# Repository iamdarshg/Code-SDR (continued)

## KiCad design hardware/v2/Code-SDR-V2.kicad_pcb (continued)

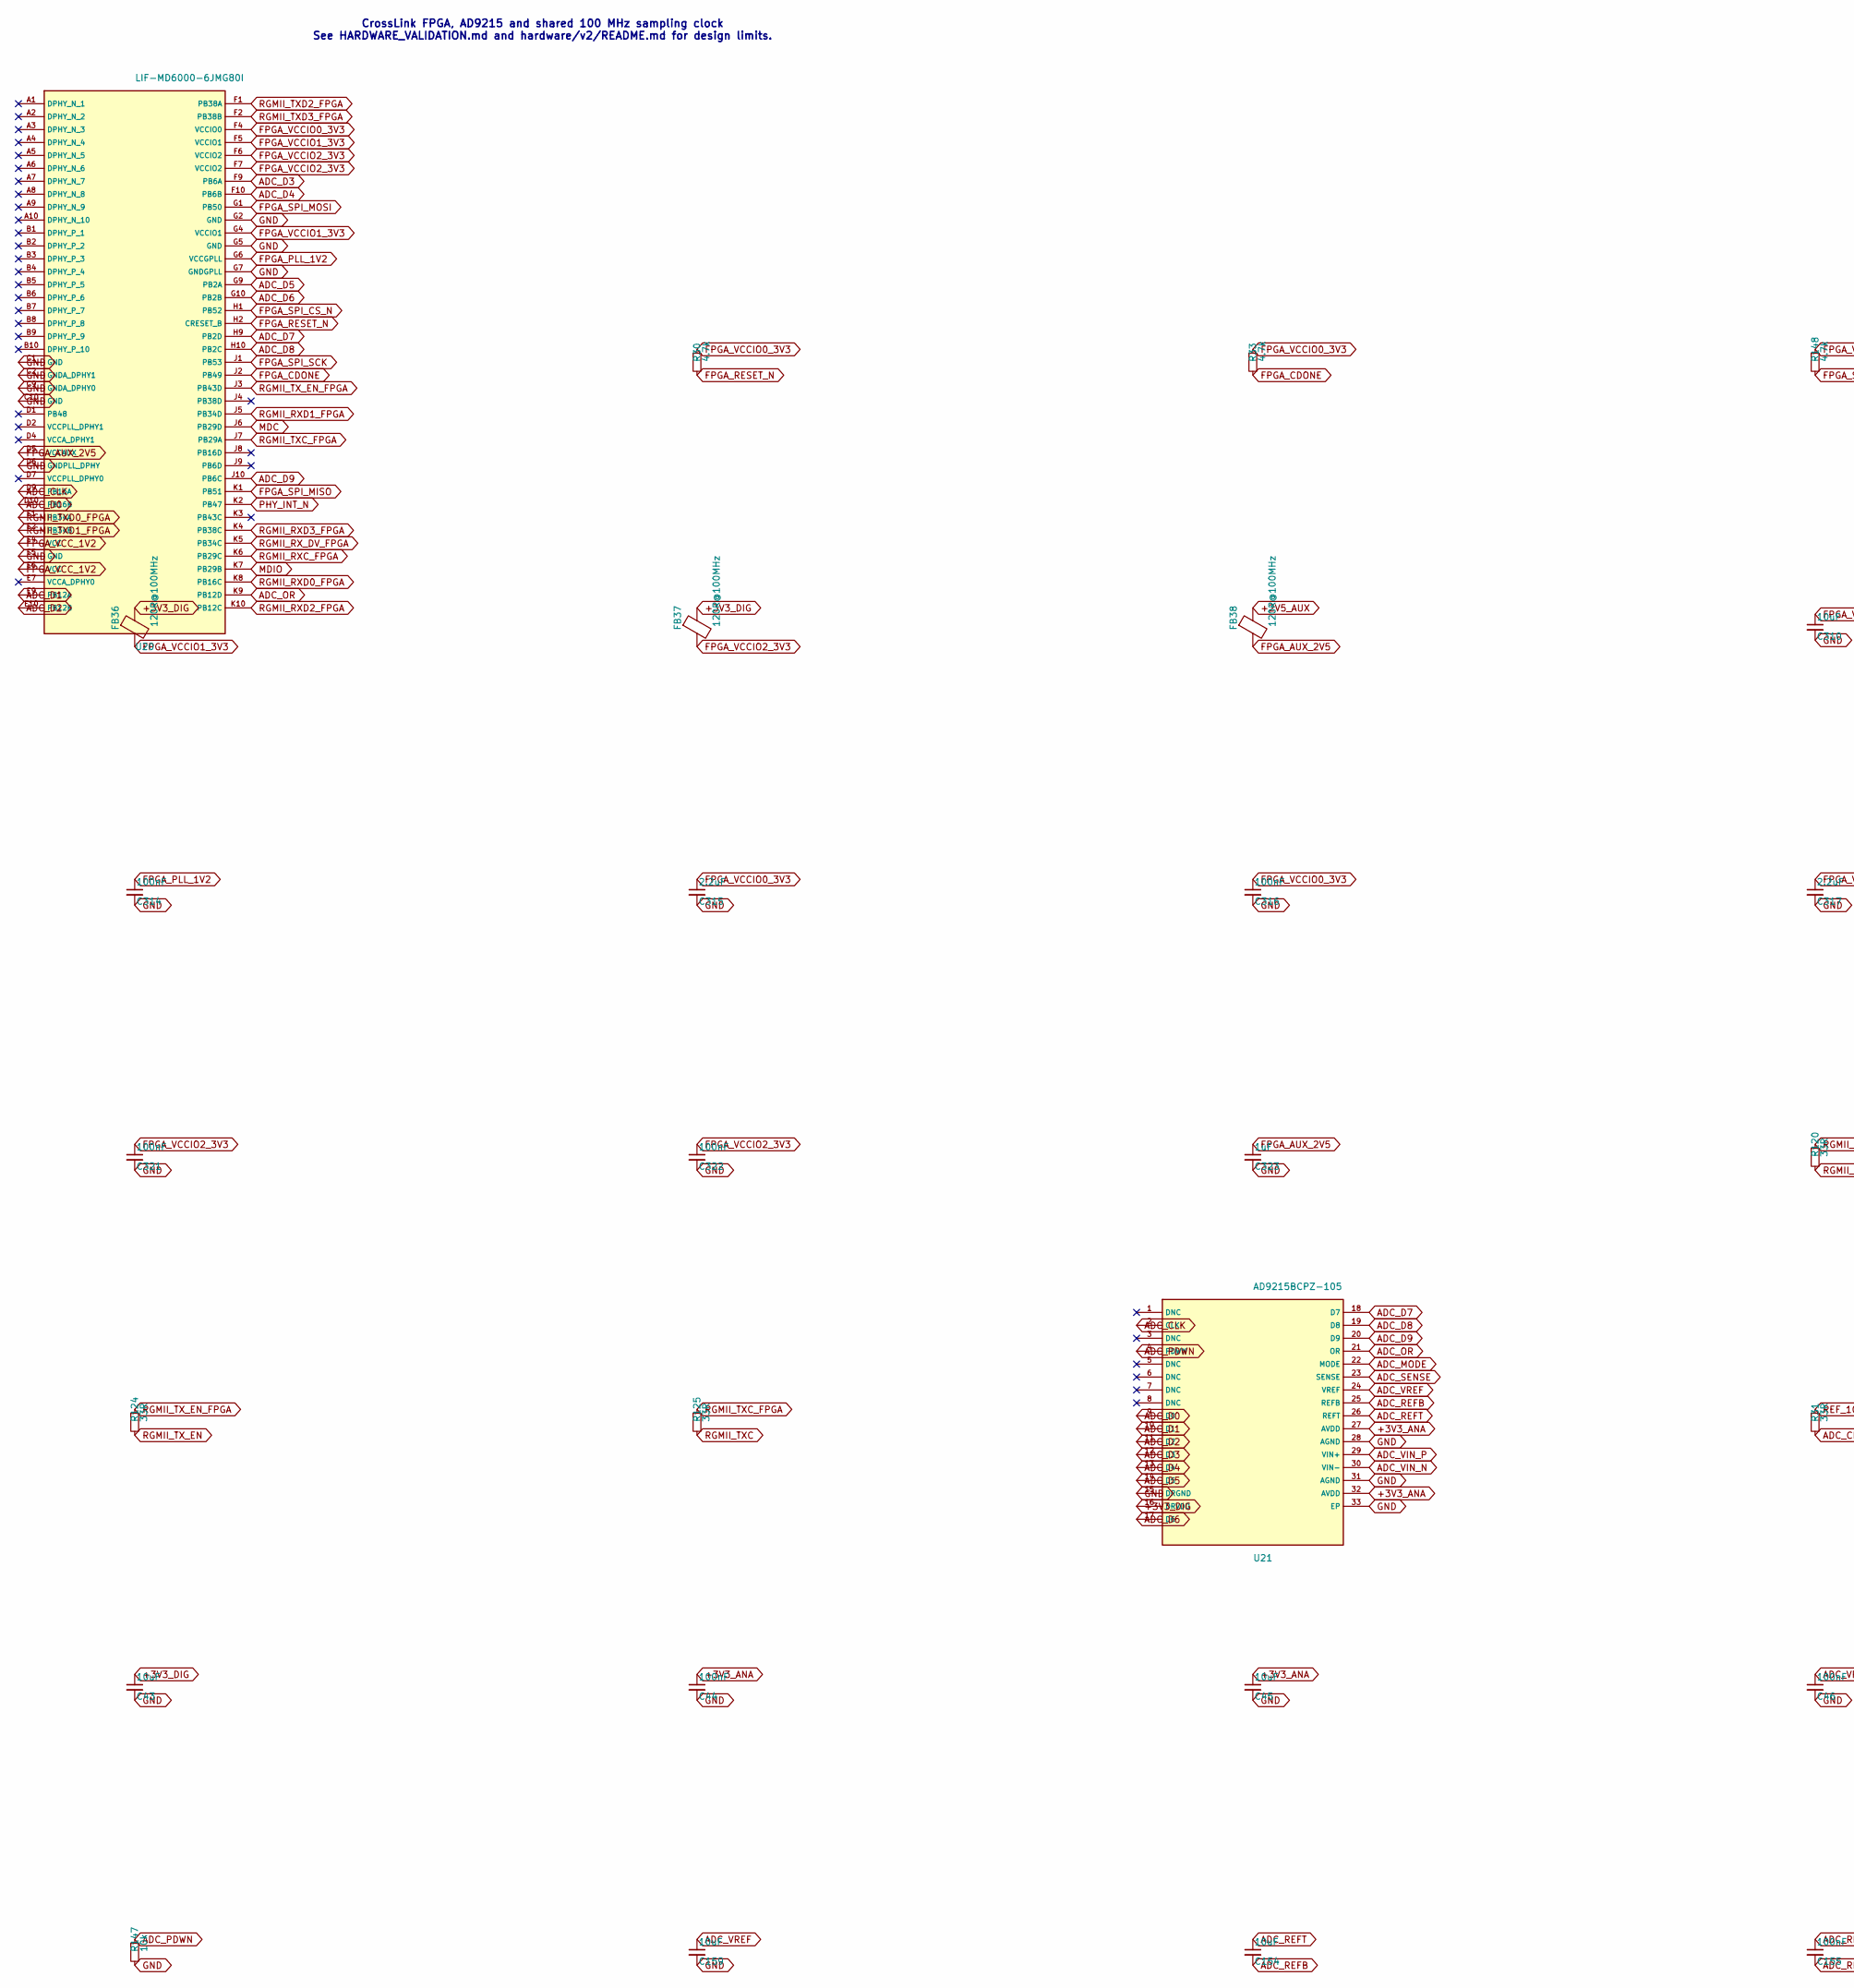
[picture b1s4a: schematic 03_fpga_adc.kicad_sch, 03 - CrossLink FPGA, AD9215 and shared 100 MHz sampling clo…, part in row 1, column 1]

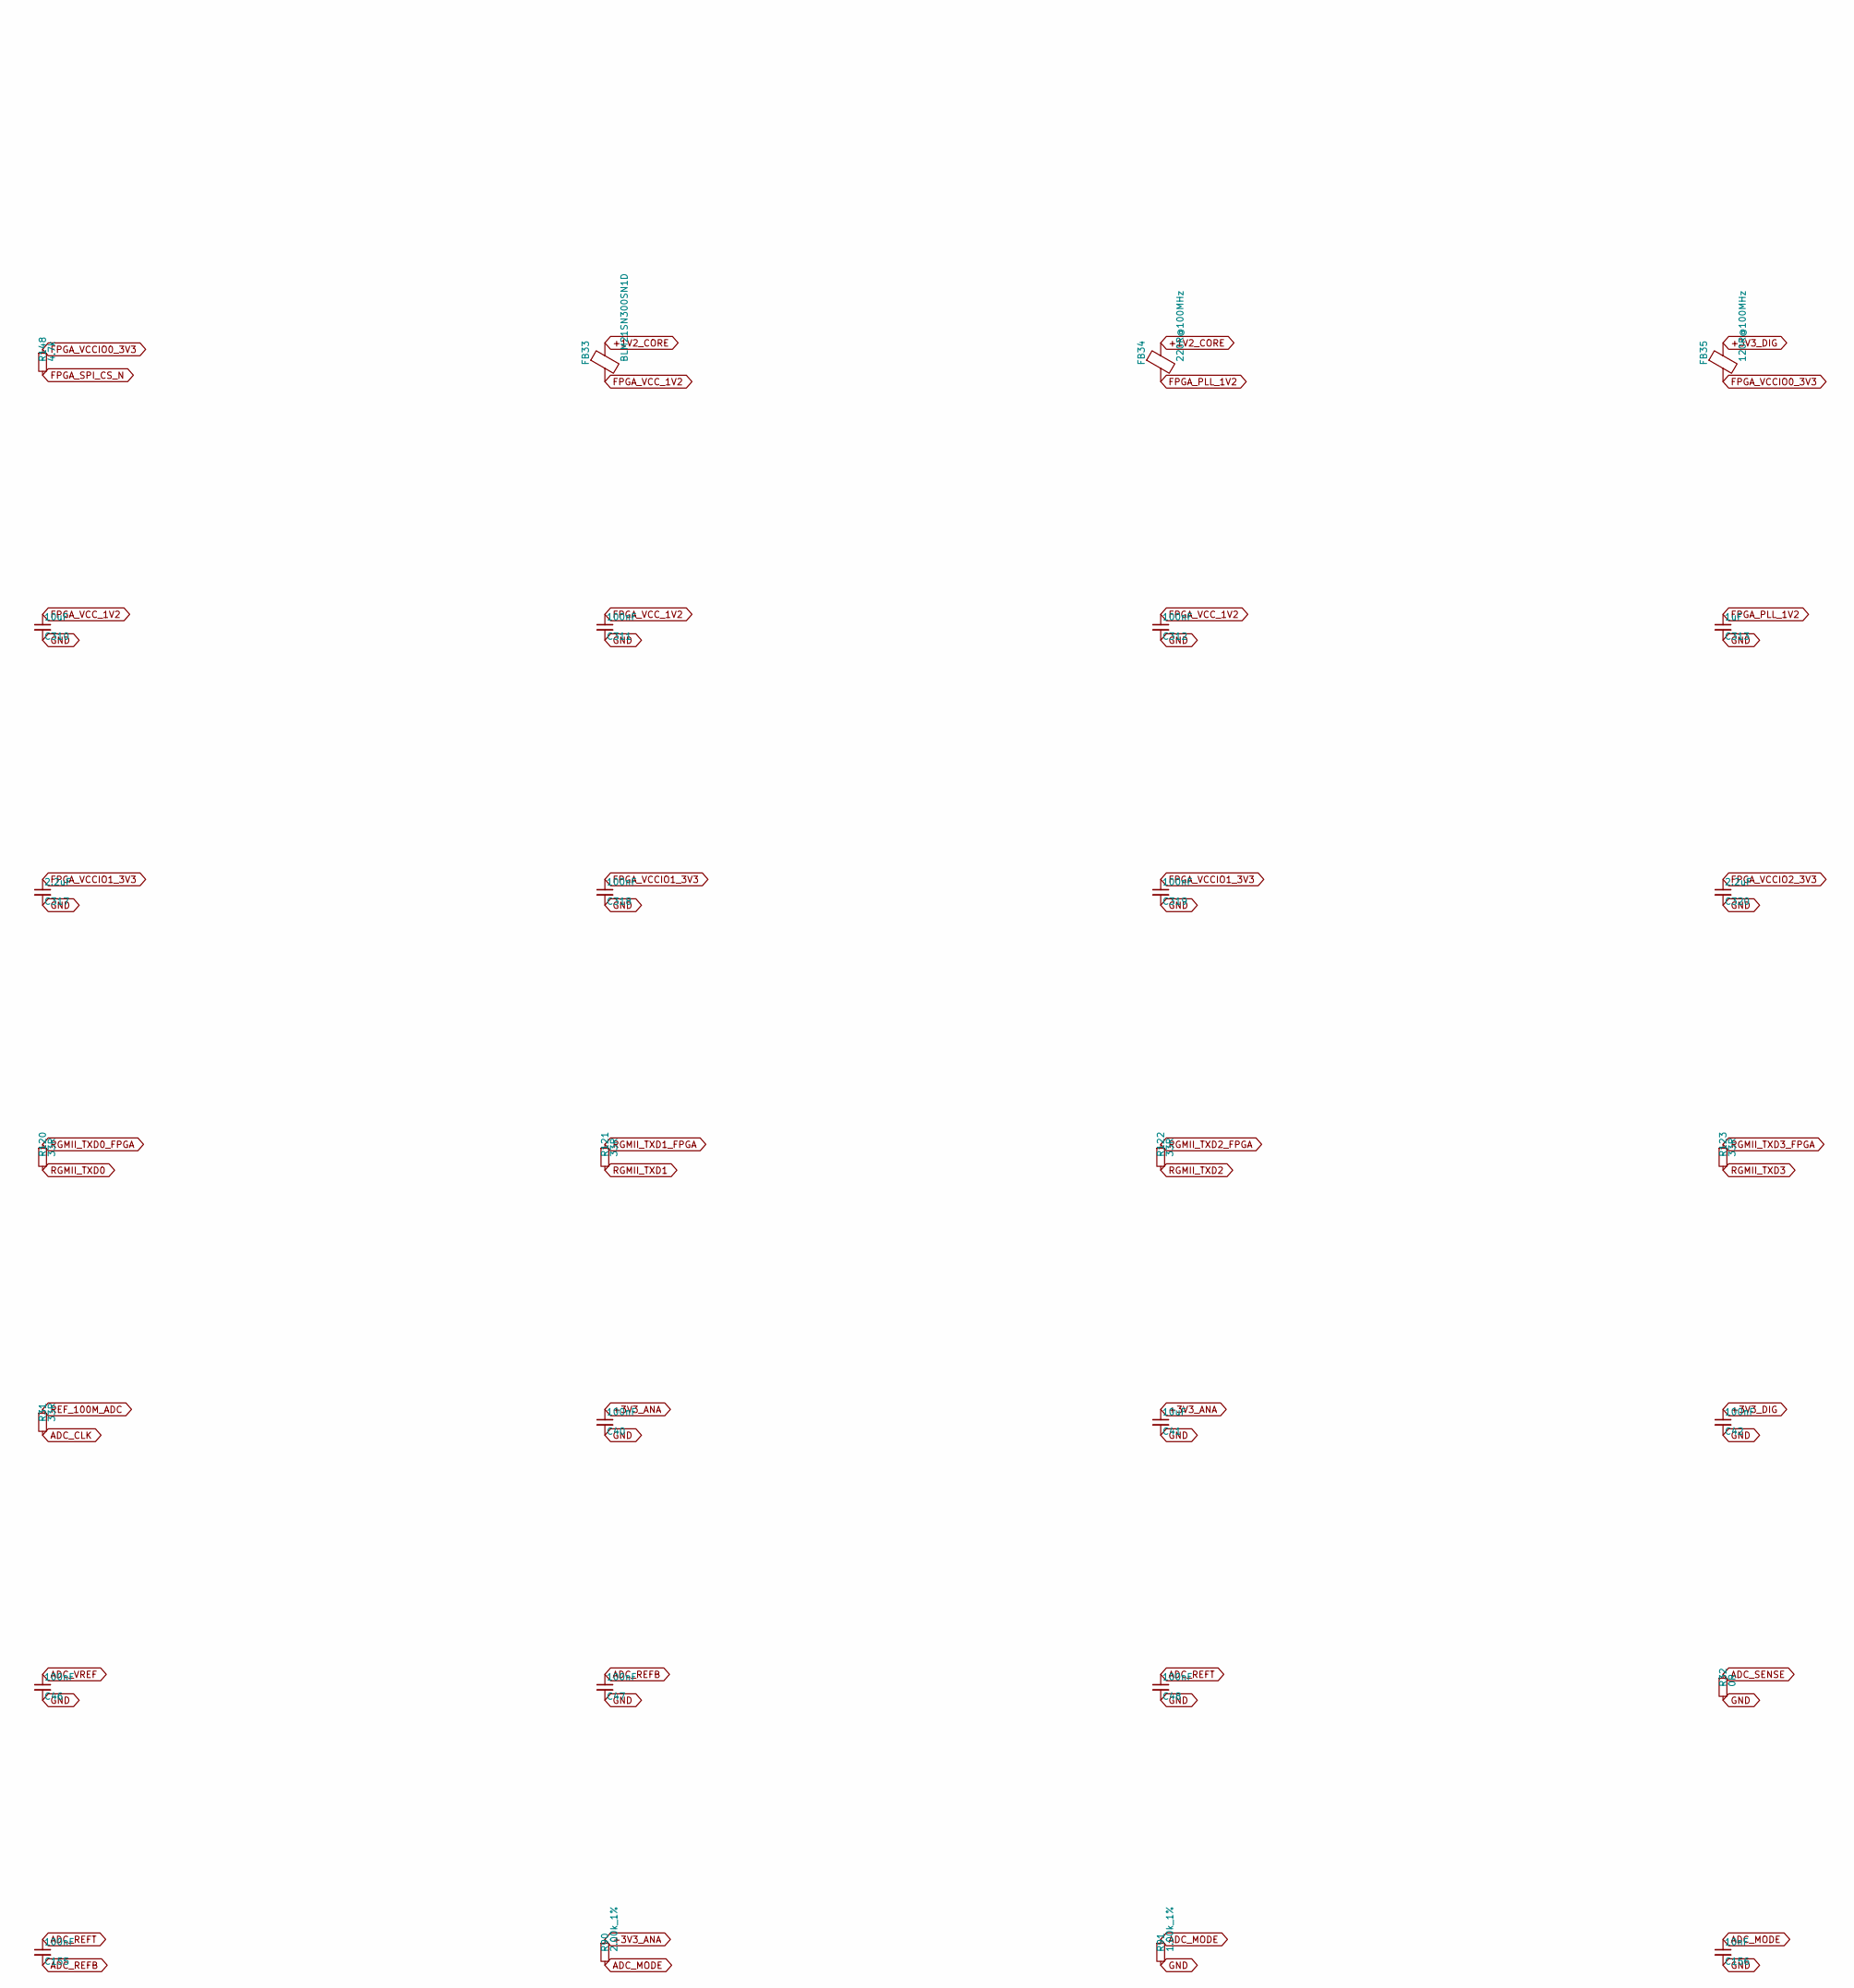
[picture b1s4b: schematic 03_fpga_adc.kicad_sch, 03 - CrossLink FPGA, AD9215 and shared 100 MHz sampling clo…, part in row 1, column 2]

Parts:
C40, C42, C44, C46, C47, C48, C155, C311, C312, C314, C316, C318, C319, C321, C322: 100nF; C_0402_1005Metric
C41, C43, C45, C154, C159, C310: 10uF; C_0805_2012Metric
C156: 10nF; C_0402_1005Metric
C313, C323: 1uF; C_0402_1005Metric
C315, C317, C320: 2.2uF; C_0402_1005Metric
FB33: BLM21SN300SN1D; L_0805_2012Metric
FB34: 220R@100MHz; L_0402_1005Metric
FB35, FB36, FB37, FB38: 120R@100MHz; L_0402_1005Metric
R30, R33, R148: 4.7k; R_0402_1005Metric
R31, R120, R121, R122, R123, R124, R125: 33R; R_0402_1005Metric
R32: 0R; R_0402_1005Metric
R90: 2.00k_1%; R_0402_1005Metric
R91: 1.00k_1%; R_0402_1005Metric
R147: 10k; R_0402_1005Metric
U20: LIF-MD6000-6JMG80I
U21: AD9215BCPZ-105; LFCSP-32-1EP_5x5mm_P0.5mm_EP3.6x3.6mm_ThermalVias

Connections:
+1V2_CORE: FB33.1, FB34.1; also elsewhere on the board
+2V5_AUX: FB38.1; also elsewhere on the board
+3V3_ANA: C40.1, C41.1, C44.1, C45.1, R90.1, U21.27 (AVDD), U21.32 (AVDD); also elsewhere on the board
ADC_CLK: R31.2, U20.D9 (PB16A), U21.2 (CLK)
ADC_D0: U20.D10 (PB16B), U21.9 (D0)
ADC_D1: U20.E9 (PB12A), U21.10 (D1)
ADC_D2: U20.E10 (PB12B), U21.11 (D2)
ADC_D3: U20.F9 (PB6A), U21.12 (D3)
ADC_D4: U20.F10 (PB6B), U21.13 (D4)
ADC_D5: U20.G9 (PB2A), U21.14 (D5)
ADC_D6: U20.G10 (PB2B), U21.17 (D6)
ADC_D7: U20.H9 (PB2D), U21.18 (D7)
ADC_D8: U20.H10 (PB2C), U21.19 (D8)
ADC_D9: U20.J10 (PB6C), U21.20 (D9)
ADC_MODE: C156.1, R90.2, R91.1, U21.22 (MODE)
ADC_OR: U20.K9 (PB12D), U21.21 (OR); also elsewhere on the board
ADC_PDWN: R147.1, U21.4 (PDWN); also elsewhere on the board
ADC_REFB: C47.1, C154.2, C155.2, U21.25 (REFB)
ADC_REFT: C48.1, C154.1, C155.1, U21.26 (REFT)
ADC_SENSE: R32.1, U21.23 (SENSE)
ADC_VIN_N: U21.30 (VIN-); also elsewhere on the board
ADC_VIN_P: U21.29 (VIN+); also elsewhere on the board
ADC_VREF: C46.1, C159.1, U21.24 (VREF)
FPGA_AUX_2V5: C323.1, FB38.2, U20.D5 (VCCAUX)
FPGA_CDONE: R33.2, U20.J2 (PB49); also elsewhere on the board
FPGA_PLL_1V2: C313.1, C314.1, FB34.2, U20.G6 (VCCGPLL)
FPGA_RESET_N: R30.2, U20.H2 (CRESET_B); also elsewhere on the board
FPGA_SPI_CS_N: R148.2, U20.H1 (PB52); also elsewhere on the board
FPGA_SPI_MISO: U20.K1 (PB51); also elsewhere on the board
FPGA_SPI_MOSI: U20.G1 (PB50); also elsewhere on the board
FPGA_SPI_SCK: U20.J1 (PB53); also elsewhere on the board
FPGA_VCCIO0_3V3: C315.1, C316.1, FB35.2, R30.1, R33.1, R148.1, U20.F4 (VCCIO0); also elsewhere on the board
FPGA_VCCIO1_3V3: C317.1, C318.1, C319.1, FB36.2, U20.F5 (VCCIO1), U20.G4 (VCCIO1); also elsewhere on the board
FPGA_VCCIO2_3V3: C320.1, C321.1, C322.1, FB37.2, U20.F6 (VCCIO2), U20.F7 (VCCIO2); also elsewhere on the board
FPGA_VCC_1V2: C310.1, C311.1, C312.1, FB33.2, U20.E4 (VCC), U20.E6 (VCC); also elsewhere on the board
MDC: U20.J6 (PB29D); also elsewhere on the board
MDIO: U20.K7 (PB29B); also elsewhere on the board
PHY_INT_N: U20.K2 (PB47); also elsewhere on the board
REF_100M_ADC: R31.1; also elsewhere on the board
RGMII_RXC_FPGA: U20.K6 (PB29C); also elsewhere on the board
RGMII_RXD0_FPGA: U20.K8 (PB16C); also elsewhere on the board
RGMII_RXD1_FPGA: U20.J5 (PB34D); also elsewhere on the board
RGMII_RXD2_FPGA: U20.K10 (PB12C); also elsewhere on the board
RGMII_RXD3_FPGA: U20.K4 (PB38C); also elsewhere on the board
RGMII_RX_DV_FPGA: U20.K5 (PB34C); also elsewhere on the board
RGMII_TXC: R125.2; also elsewhere on the board
RGMII_TXC_FPGA: R125.1, U20.J7 (PB29A)
RGMII_TXD0: R120.2; also elsewhere on the board
RGMII_TXD0_FPGA: R120.1, U20.E1 (PB34A)
RGMII_TXD1: R121.2; also elsewhere on the board
RGMII_TXD1_FPGA: R121.1, U20.E2 (PB34B)
RGMII_TXD2: R122.2; also elsewhere on the board
RGMII_TXD2_FPGA: R122.1, U20.F1 (PB38A)
RGMII_TXD3: R123.2; also elsewhere on the board
RGMII_TXD3_FPGA: R123.1, U20.F2 (PB38B)
RGMII_TX_EN: R124.2; also elsewhere on the board
RGMII_TX_EN_FPGA: R124.1, U20.J3 (PB43D)

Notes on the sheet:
CrossLink FPGA, AD9215 and shared 100 MHz sampling clock See HARDWARE_VALIDATION.md and hardware/v2/README.md for design limits.
